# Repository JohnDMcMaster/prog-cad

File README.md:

# prog-cad

Misc programmer adapters

Related repos:
* ZSM repository: https://github.com/Labsmore/zscn-sm
  * Industrial socket modules with up to 160 package GPIOs, EEPROM to identify module, etc
  * Loosely compatible with BP Microsystems
  * See spec: https://docs.google.com/document/d/1DNgjsjrHdlfkA_atRu-mPDHIEeETf2TU_p970Pdej90/edit#
  * Currently private, plan to release at confernece talk
* TL866 aggregator: https://github.com/JohnDMcMaster/mega866-cad/
  * Takes ZSM / BPM socket modules
* BP Microsystems USB adapter: https://github.com/JohnDMcMaster/bpm-usb
  * Convert a parallel port programmer to USB
  * Based on the official USB adapter
  * WARNING: board bring up failed / unreliable
* Wire bonding adapters: https://github.com/JohnDMcMaster/bond-pcb
  * TODO: many more to add

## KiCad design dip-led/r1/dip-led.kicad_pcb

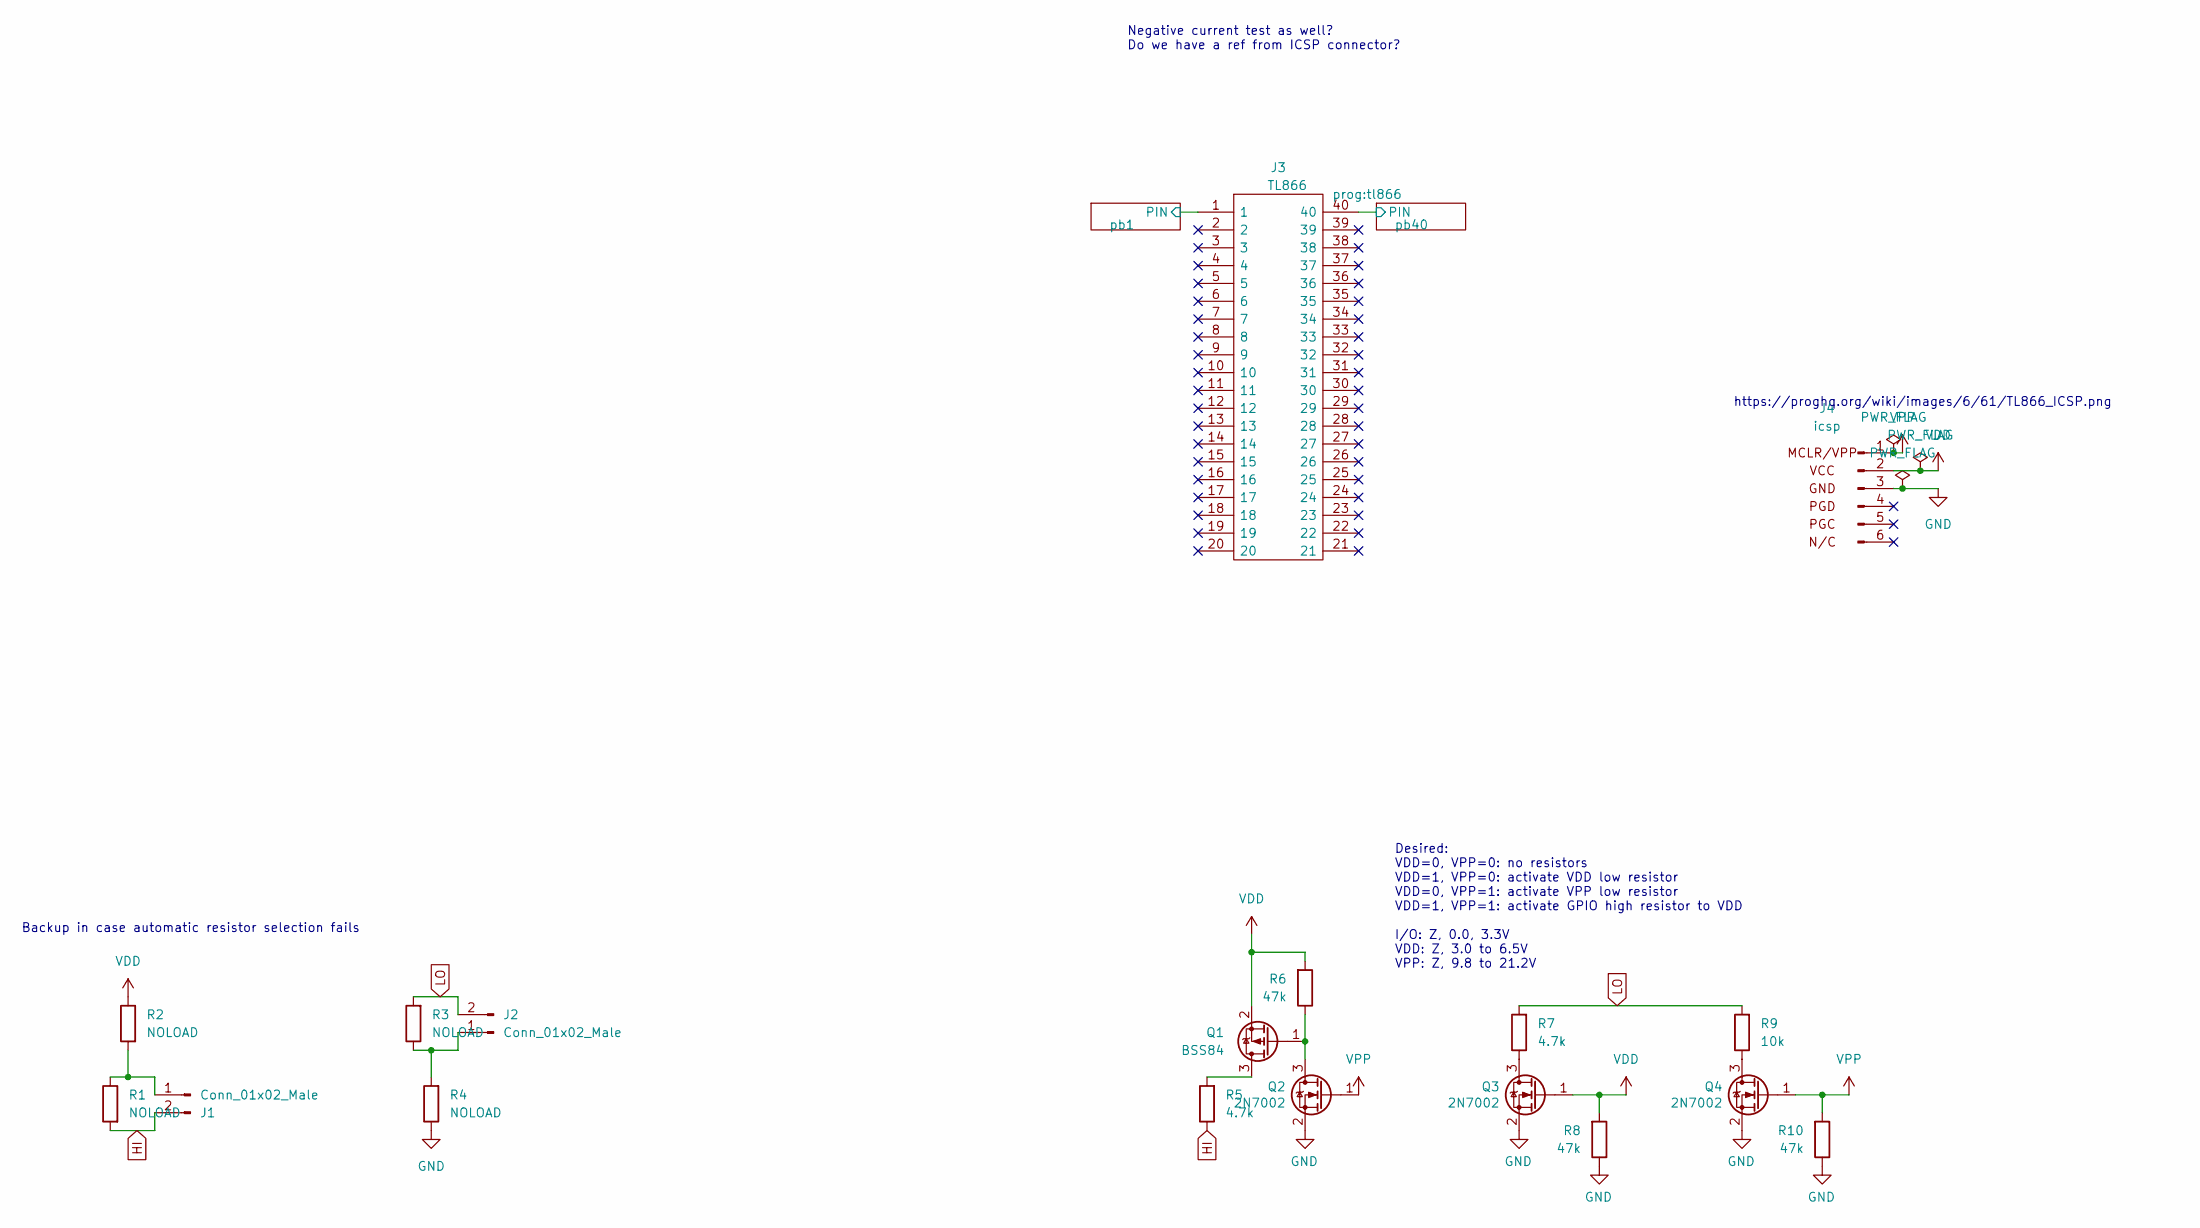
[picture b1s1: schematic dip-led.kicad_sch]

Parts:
J1, J2: Conn_01x02_Male; PinHeader_1x02_P2.54mm_Vertical
J3: TL866; tl866
J4: icsp; PinHeader_1x06_P2.54mm_Vertical
Q1: BSS84; SOT-23
Q2, Q3, Q4: 2N7002; SOT-23
R1, R2, R3, R4: NOLOAD; R_0603_1608Metric
R5, R7: 4.7k; R_0603_1608Metric
R6, R8, R10: 47k; R_0603_1608Metric
R9: 10k; R_0603_1608Metric

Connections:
/pb1/PIN: J3.1; also elsewhere on the board
/pb40/PIN: J3.40; also elsewhere on the board
GND: J4.3, Q2.2 (S), Q3.2 (S), Q4.2 (S), R4.1, R8.1, R10.1
HI: J1.2, R1.2, R5.1; also elsewhere on the board
LO: J2.2, R3.2, R7.2, R9.2; also elsewhere on the board
unnamed: J1.1, R1.1, R2.2
unnamed: J2.1, R3.1, R4.2
unnamed: Q1.1 (G), Q2.3 (D), R6.1
unnamed: Q1.3 (D), R5.2
unnamed: Q3.3 (D), R7.1
unnamed: Q4.3 (D), R9.1
VDD: J4.2, Q1.2 (S), Q3.1 (G), R2.1, R6.2, R8.2
VPP: J4.1 (VPP/MCLR), Q2.1 (G), Q4.1 (G), R10.2

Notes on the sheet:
Backup in case automatic resistor selection fails
Desired: VDD=0, VPP=0: no resistors VDD=1, VPP=0: activate VDD low resistor VDD=0, VPP=1: activate VPP low resistor VDD=1, VPP=1: activate GPIO high resistor to VDD I/O: Z, 0.0, 3.3V VDD: Z, 3.0 to 6.5V VPP: Z, 9.8 to 21.2V
https://proghq.org/wiki/images/6/61/TL866_ICSP.png
Negative current test as well? Do we have a ref from ICSP connector?

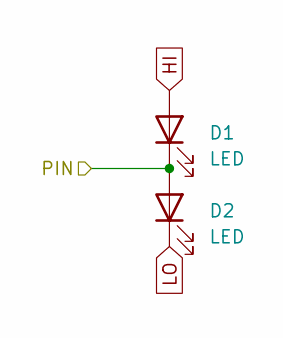
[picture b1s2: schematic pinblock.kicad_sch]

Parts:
D1, D2: LED; LED_0603_1608Metric

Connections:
/pb1/PIN: D1.1 (K), D2.2 (A); also elsewhere on the board
HI: D1.2 (A); also elsewhere on the board
LO: D2.1 (K); also elsewhere on the board

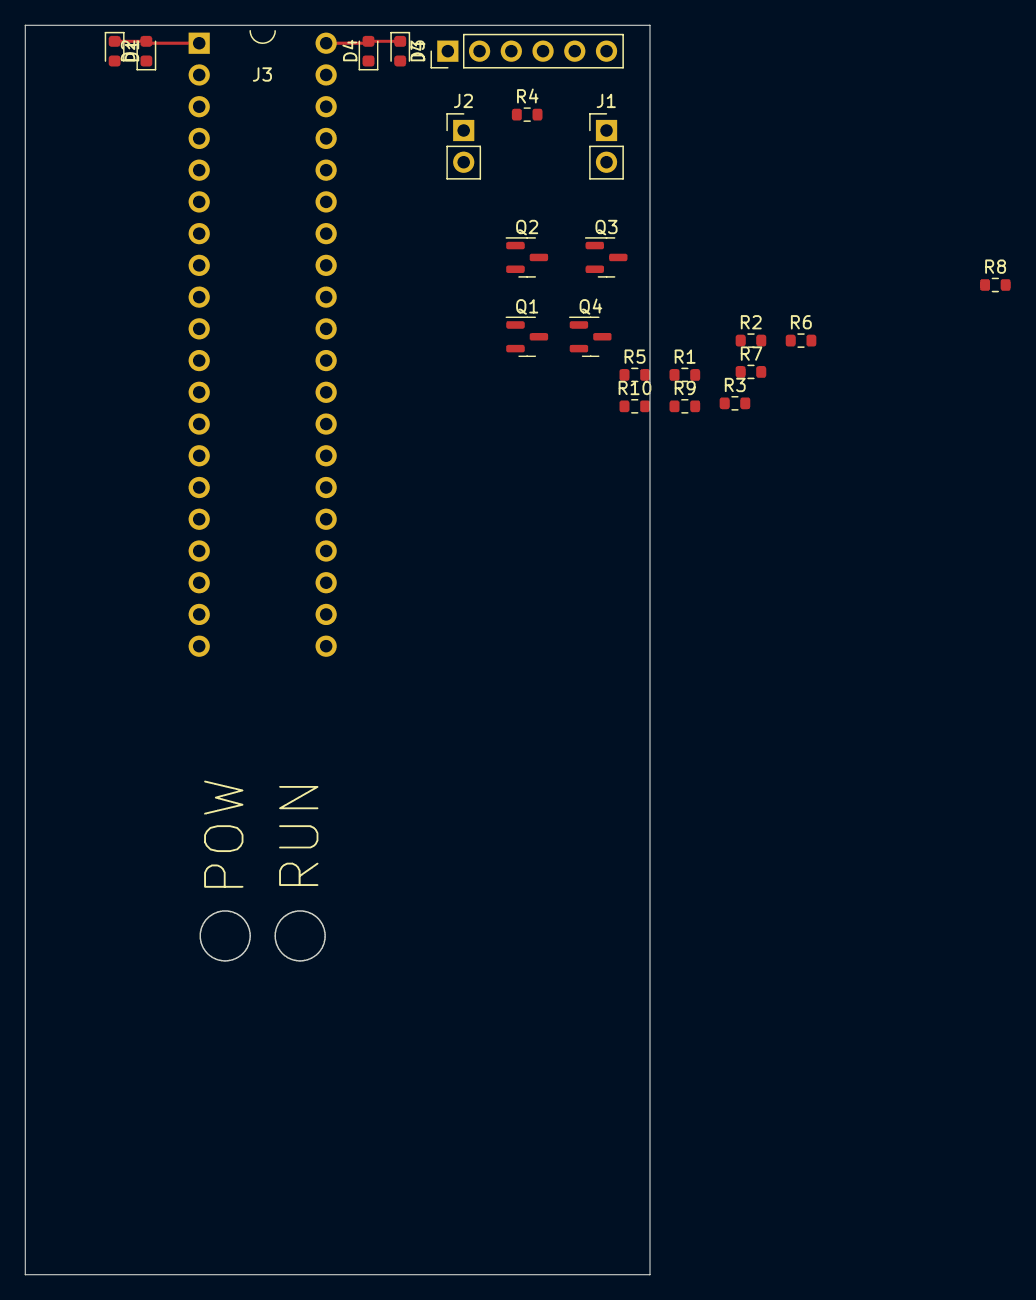
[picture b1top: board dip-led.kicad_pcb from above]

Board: 2 copper layers, 50.0 x 100.0 mm, 22 parts (0 on the bottom side), 13 nets.

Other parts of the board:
D3, D4: LED; LED_0603_1608Metric

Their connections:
/pb40/PIN: D3.1 (K), D4.2 (A); also elsewhere on the board
HI: D3.2 (A); also elsewhere on the board
LO: D4.1 (K); also elsewhere on the board

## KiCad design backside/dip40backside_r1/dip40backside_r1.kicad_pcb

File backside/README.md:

# icbackside
IC backside adapters

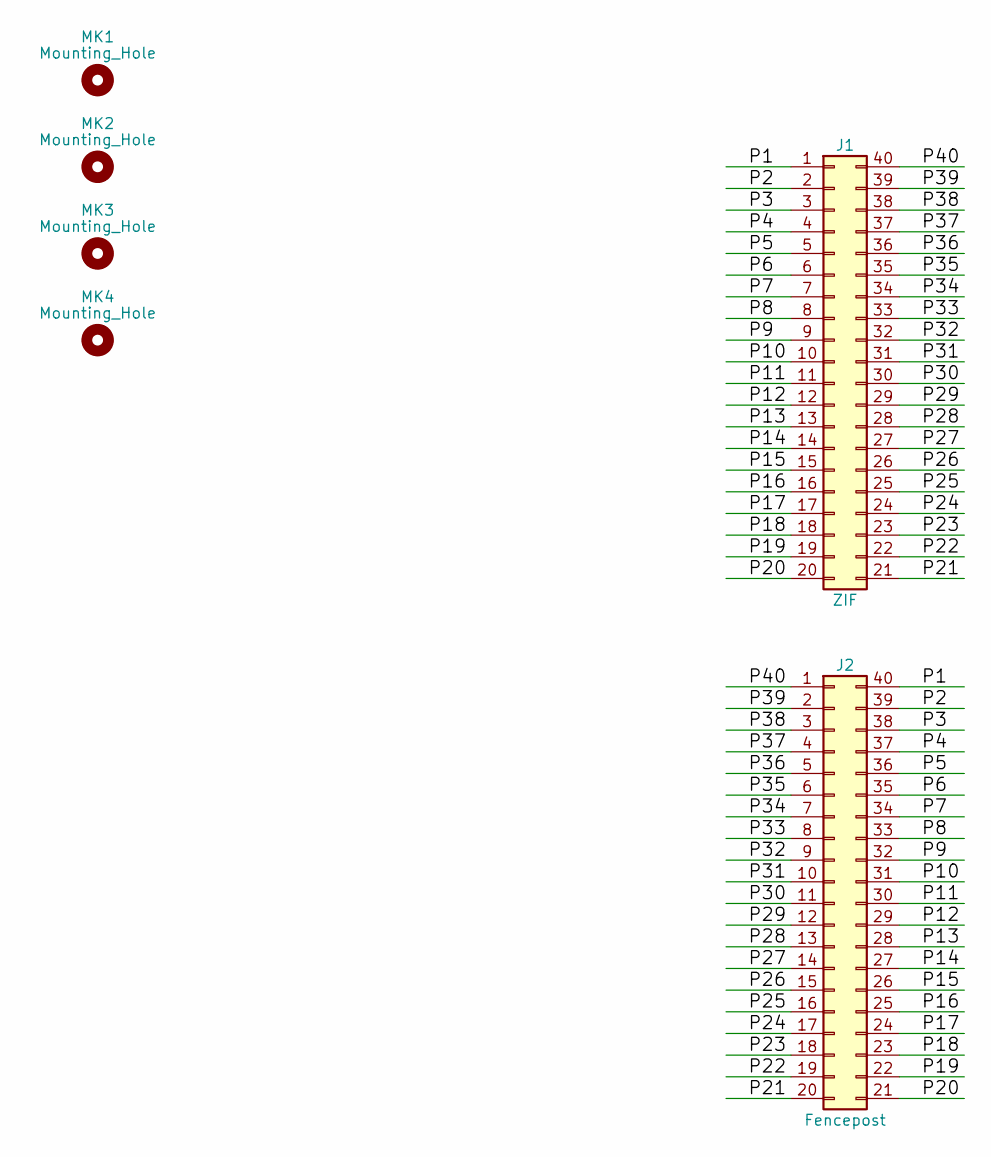
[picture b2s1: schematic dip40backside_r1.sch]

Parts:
J1: ZIF; aries_40-6554-10_DIP-40_W15.24mm_ZIF
J2: Fencepost; dip40-0.3
MK1, MK2, MK3, MK4: Mounting_Hole; MountingHole_8.4mm_M8

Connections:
/P1: J1.1, J2.40
/P2: J1.2, J2.39
/P3: J1.3, J2.38
/P4: J1.4, J2.37
/P5: J1.5, J2.36
/P6: J1.6, J2.35
/P7: J1.7, J2.34
/P8: J1.8, J2.33
/P9: J1.9, J2.32
/P10: J1.10, J2.31
/P11: J1.11, J2.30
/P12: J1.12, J2.29
/P13: J1.13, J2.28
/P14: J1.14, J2.27
/P15: J1.15, J2.26
/P16: J1.16, J2.25
/P17: J1.17, J2.24
/P18: J1.18, J2.23
/P19: J1.19, J2.22
/P20: J1.20, J2.21
/P21: J1.21, J2.20
/P22: J1.22, J2.19
/P23: J1.23, J2.18
/P24: J1.24, J2.17
/P25: J1.25, J2.16
/P26: J1.26, J2.15
/P27: J1.27, J2.14
/P28: J1.28, J2.13
/P29: J1.29, J2.12
/P30: J1.30, J2.11
/P31: J1.31, J2.10
/P32: J1.32, J2.9
/P33: J1.33, J2.8
/P34: J1.34, J2.7
/P35: J1.35, J2.6
/P36: J1.36, J2.5
/P37: J1.37, J2.4
/P38: J1.38, J2.3
/P39: J1.39, J2.2
/P40: J1.40, J2.1

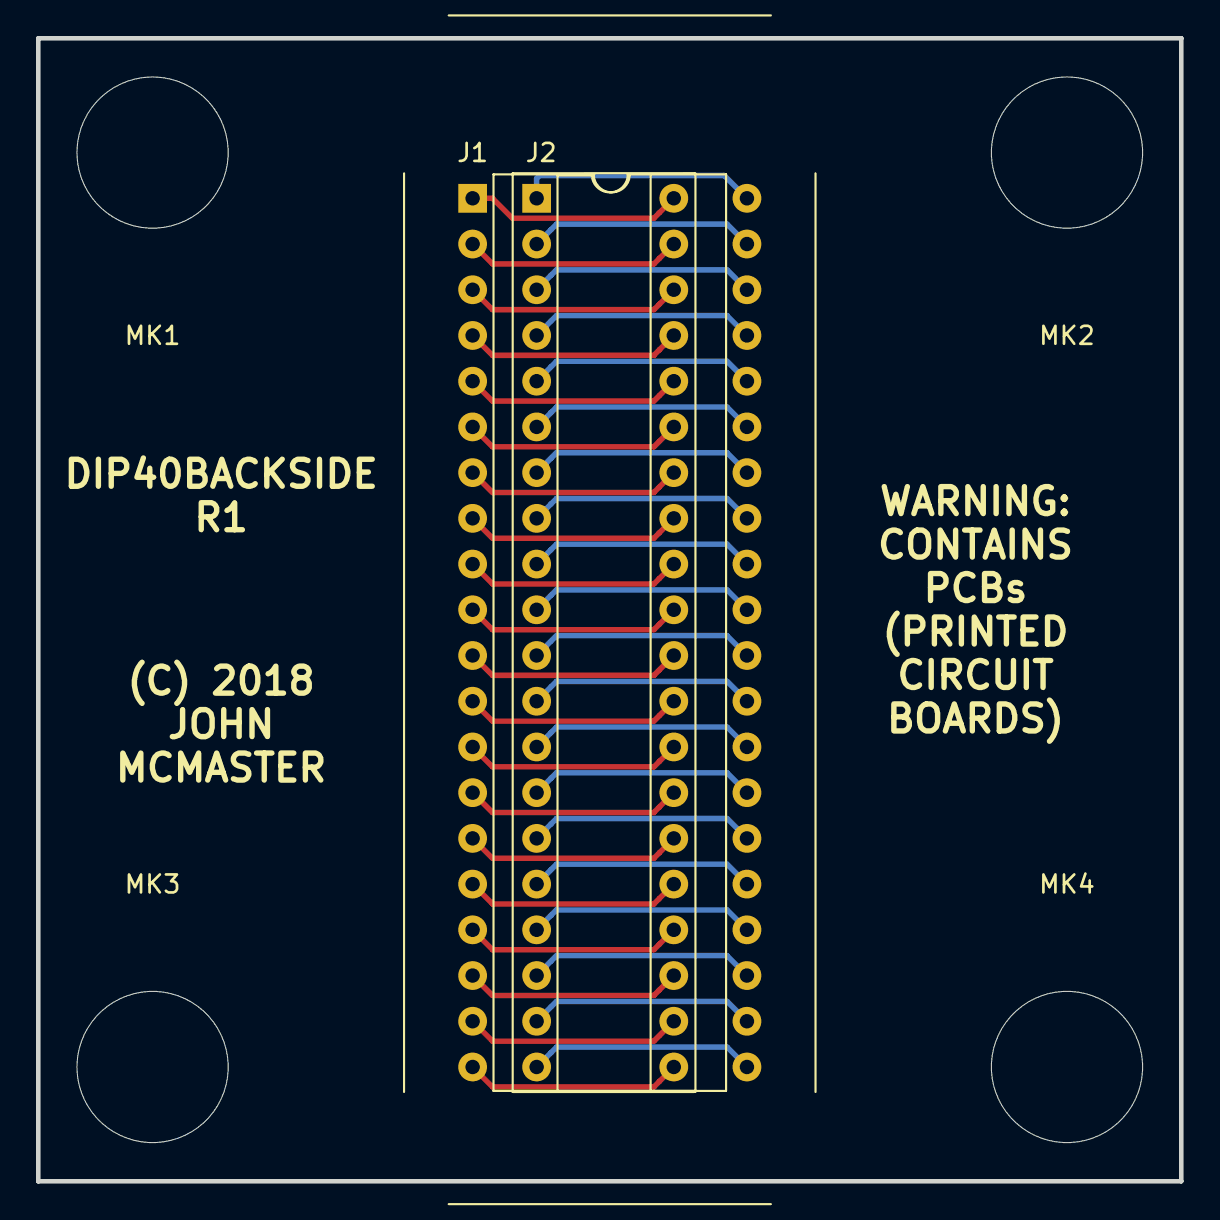
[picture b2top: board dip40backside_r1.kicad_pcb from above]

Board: 2 copper layers, 63.5 x 63.5 mm, 6 parts (0 on the bottom side), 40 nets.

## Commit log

2018-08-07 dip40spy_r1
2018-08-09 gitignore
2022-10-16 shuffle
2022-10-16 dip40 backside
2022-10-16 bpm-socket
2022-10-16 note
2022-10-16 readme links
2022-11-02 dip-led WIP

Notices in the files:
backside/dip40backside_r1/dip40backside_r1.kicad_pcb:
(C) 2018
